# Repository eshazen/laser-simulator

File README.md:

# laser-simulator
Simple simulator for type A laser

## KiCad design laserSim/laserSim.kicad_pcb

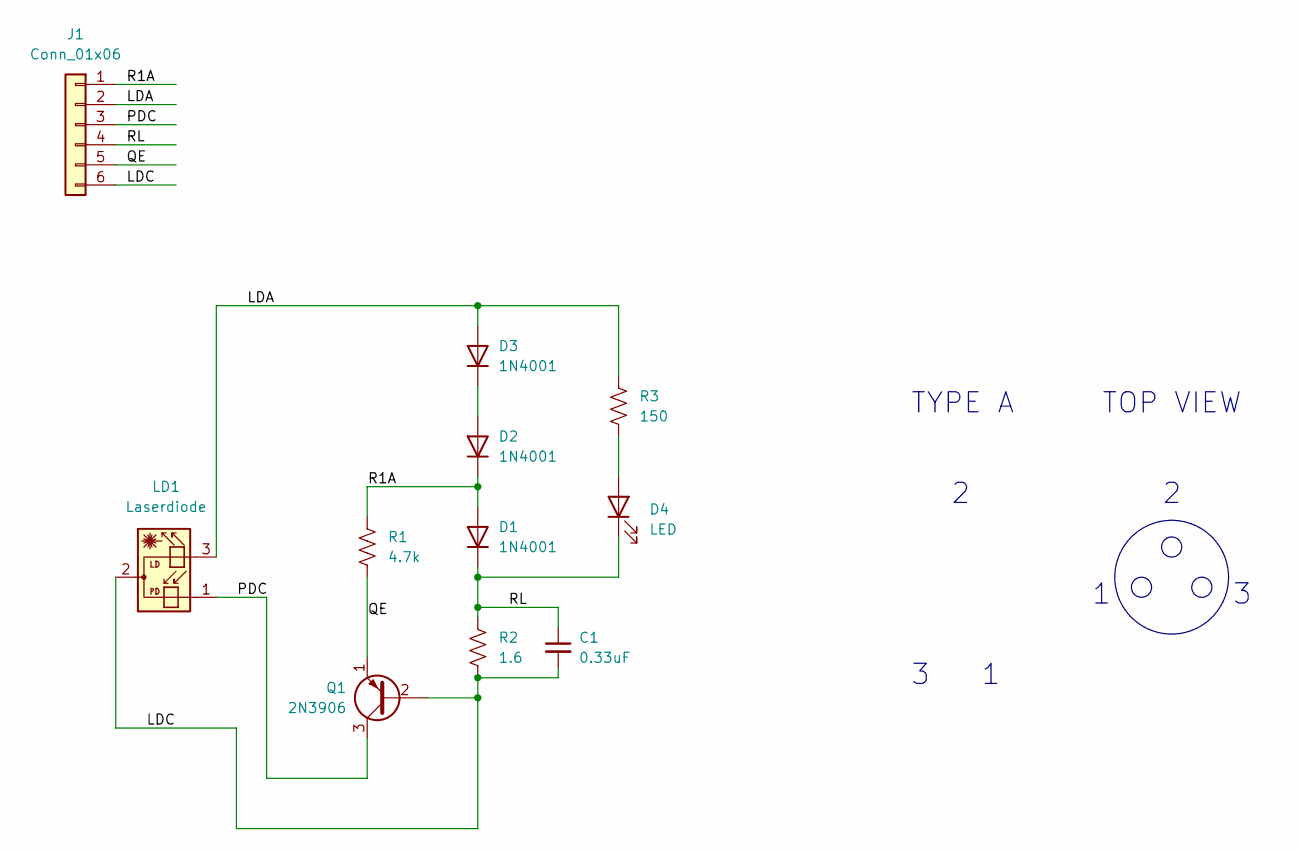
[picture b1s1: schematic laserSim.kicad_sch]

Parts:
C1: 0.33uF; C_Disc_D3.0mm_W1.6mm_P2.50mm
D1, D2, D3: 1N4001; D_DO-41_SOD81_P2.54mm_Vertical_KathodeUp
D4: LED; LED_D3.0mm
J1: Conn_01x06; PinHeader_1x06_P2.54mm_Vertical
LD1: Laserdiode; laserDiode
Q1: 2N3906; TO-92_Inline_Wide
R1: 4.7k; R_Axial_DIN0207_L6.3mm_D2.5mm_P2.54mm_Vertical
R2: 1.6; R_Axial_DIN0207_L6.3mm_D2.5mm_P2.54mm_Vertical
R3: 150; R_Axial_DIN0207_L6.3mm_D2.5mm_P2.54mm_Vertical

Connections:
/LDA: D3.2 (A), J1.2, LD1.3, R3.1
/LDC: C1.2, J1.6, LD1.2, Q1.2 (B), R2.2
/PDC: J1.3, LD1.1, Q1.3 (C)
/QE: J1.5, Q1.1 (E), R1.2
/R1A: D1.2 (A), D2.1 (K), J1.1, R1.1
/RL: C1.1, D1.1 (K), D4.1 (K), J1.4, R2.1
unnamed: D2.2 (A), D3.1 (K)
unnamed: D4.2 (A), R3.2

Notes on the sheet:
TOP VIEW
TYPE A

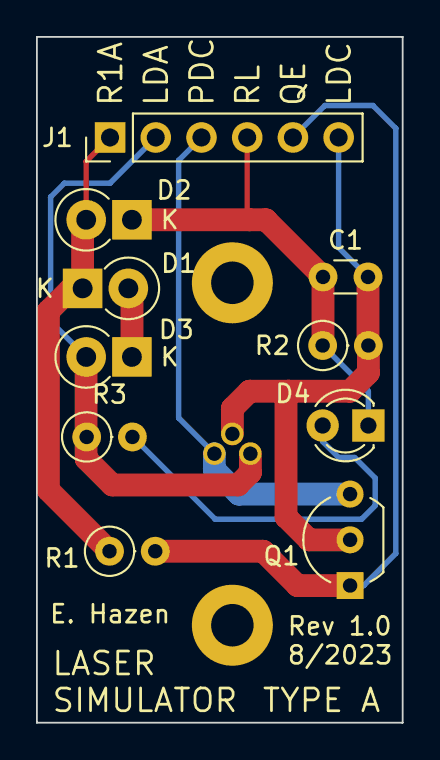
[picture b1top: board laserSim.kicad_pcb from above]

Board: 2 copper layers, 20.3 x 38.1 mm, 11 parts (1 on the bottom side), 8 nets.

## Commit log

2023-08-24 initial commit after fab of Rev 1
2023-08-24 pictures
